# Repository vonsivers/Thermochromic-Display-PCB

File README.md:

# Thermochromic-Display-PCB
 Thermochromic Temperature & Humidity Display - PCB Version

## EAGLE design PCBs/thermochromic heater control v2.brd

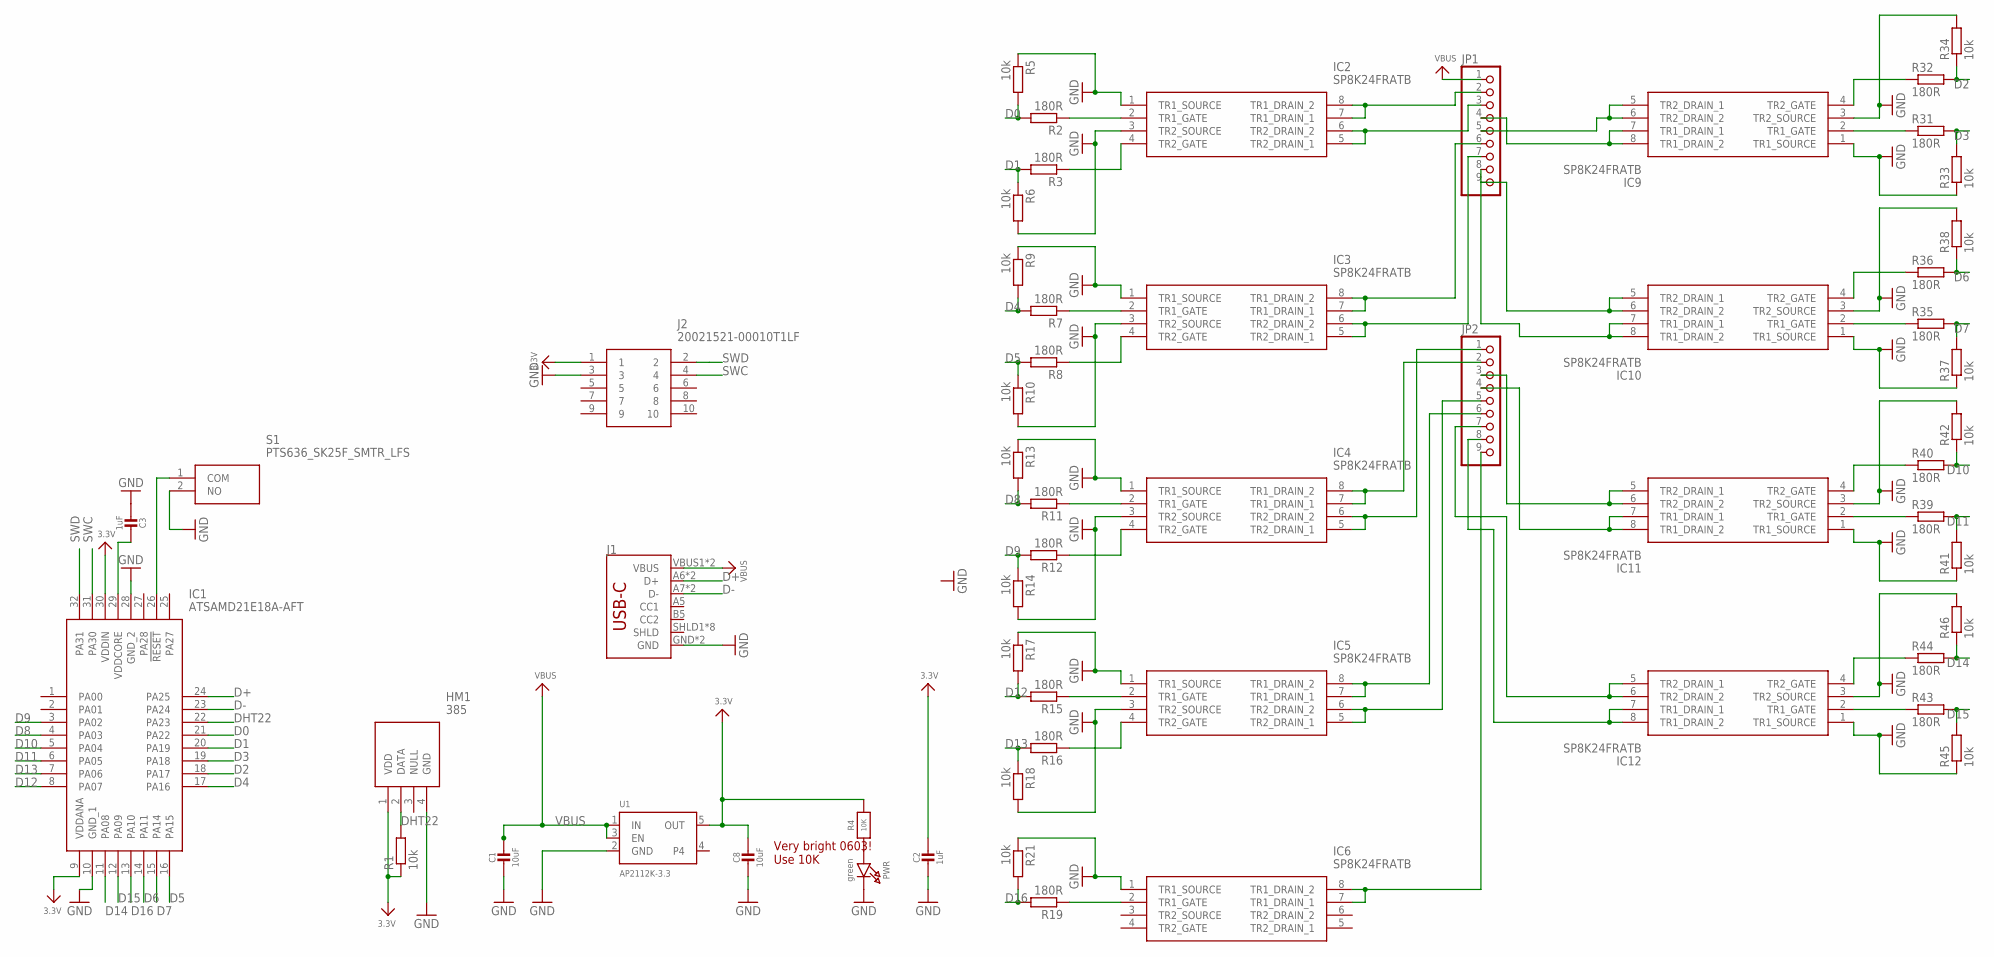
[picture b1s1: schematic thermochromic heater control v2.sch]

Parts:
C1, C8: 10uF; 0805-NO
C2, C3: 1uF; 0603-NO
HM1: 385; TO200P770X1510X2520-4P
IC1: ATSAMD21E18A-AFT; QFP80P900X900X120-32N
IC2, IC3, IC4, IC5, IC6, IC9, IC10, IC11, IC12: SP8K24FRATB; SOIC127P600X175-8N
J1: USB_C2-LAYER; USB-C-16P
J2: 20021521-00010T1LF; 2002152100010T1LF
JP1, JP2: PINHD-1X9; 1X09
PWR: green; CHIPLED_0603_NOOUTLINE
R1, R5, R6, R9, R10, R13, R14, R17, R18, R21, R33, R34, R37, R38, R41, R42, R45, R46: 10k; R0603
R2, R3, R7, R8, R11, R12, R15, R16, R19, R31, R32, R35, R36, R39, R40, R43, R44: 180R; R0603
R4: 10K; 0603-NO
S1: PTS636_SK25F_SMTR_LFS; PTS636SK25FSMTRLFS
U1: AP2112K-3.3; SOT23-5

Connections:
3.3V: C2.1, C8.1, HM1.1 (VDD), IC1.9 (VDDANA), IC1.30 (VDDIN), J2.1, R1.1, R4.2, U1.5 (OUT)
D0: IC1.21 (PA22), R2.2, R5.2
D1: IC1.20 (PA19), R3.2, R6.1
D2: IC1.18 (PA17), R32.2, R34.1
D3: IC1.19 (PA18), R31.2, R33.2
D4: IC1.17 (PA16), R7.2, R9.2
D5: IC1.16 (PA15), R8.2, R10.1
D6: IC1.14 (PA11), R36.2, R38.1
D7: IC1.15 (PA14), R35.2, R37.2
D8: IC1.4 (PA03), R11.2, R13.2
D9: IC1.3 (PA02), R12.2, R14.1
D10: IC1.5 (PA04), R40.2, R42.1
D11: IC1.6 (PA05), R39.2, R41.2
D12: IC1.8 (PA07), R15.2, R17.2
D13: IC1.7 (PA06), R16.2, R18.1
D14: IC1.11 (PA08), R44.2, R46.1
D15: IC1.12 (PA09), R43.2, R45.2
D16: IC1.13 (PA10), R19.2, R21.2
D+: IC1.24 (PA25), J1.A6 (D+), J1.B6 (D+)
D-: IC1.23 (PA24), J1.A7 (D-), J1.B7 (D-)
DHT22: HM1.2 (DATA), IC1.22 (PA23), R1.2
GND: C1.2, C2.2, C3.2, C8.2, HM1.4 (GND), IC1.10 (GND_1), IC1.28 (GND_2), IC2.1 (TR1_SOURCE), IC2.3 (TR2_SOURCE), IC3.1 (TR1_SOURCE), IC3.3 (TR2_SOURCE), IC4.1 (TR1_SOURCE), IC4.3 (TR2_SOURCE), IC5.1 (TR1_SOURCE), IC5.3 (TR2_SOURCE), IC6.1 (TR1_SOURCE), IC9.1 (TR1_SOURCE), IC9.3 (TR2_SOURCE), IC10.1 (TR1_SOURCE), IC10.3 (TR2_SOURCE), IC11.1 (TR1_SOURCE), IC11.3 (TR2_SOURCE), IC12.1 (TR1_SOURCE), IC12.3 (TR2_SOURCE), J1.GND, J1.GND2 (GND), J2.3, PWR.C, R5.1, R6.2, R9.1, R10.2, R13.1, R14.2, R17.1, R18.2, R21.1, R33.1, R34.2, R37.1, R38.2, R41.1, R42.2, R45.1, R46.2, S1.2 (NO), U1.2 (GND)
unnamed: C3.1, IC1.29 (VDDCORE)
unnamed: IC2.2 (TR1_GATE), R2.1
unnamed: IC1.26 (!RESET), S1.1 (COM)
unnamed: PWR.A, R4.1
unnamed: IC2.4 (TR2_GATE), R3.1
unnamed: IC2.7 (TR1_DRAIN_1), IC2.8 (TR1_DRAIN_2), JP1.2
unnamed: IC2.5 (TR2_DRAIN_1), IC2.6 (TR2_DRAIN_2), JP1.3
unnamed: IC10.2 (TR1_GATE), R35.1
unnamed: IC3.2 (TR1_GATE), R7.1
unnamed: IC3.4 (TR2_GATE), R8.1
unnamed: IC3.7 (TR1_DRAIN_1), IC3.8 (TR1_DRAIN_2), JP1.6
unnamed: IC3.5 (TR2_DRAIN_1), IC3.6 (TR2_DRAIN_2), JP1.7
unnamed: IC4.2 (TR1_GATE), R11.1
unnamed: IC4.4 (TR2_GATE), R12.1
unnamed: IC4.7 (TR1_DRAIN_1), IC4.8 (TR1_DRAIN_2), JP2.2
unnamed: IC4.5 (TR2_DRAIN_1), IC4.6 (TR2_DRAIN_2), JP2.1
unnamed: IC5.2 (TR1_GATE), R15.1
unnamed: IC5.4 (TR2_GATE), R16.1
unnamed: IC5.7 (TR1_DRAIN_1), IC5.8 (TR1_DRAIN_2), JP2.6
unnamed: IC5.5 (TR2_DRAIN_1), IC5.6 (TR2_DRAIN_2), JP2.5
unnamed: IC6.2 (TR1_GATE), R19.1
unnamed: IC6.7 (TR1_DRAIN_1), IC6.8 (TR1_DRAIN_2), JP2.9
unnamed: IC9.2 (TR1_GATE), R31.1
unnamed: IC9.4 (TR2_GATE), R32.1
unnamed: IC9.7 (TR1_DRAIN_1), IC9.8 (TR1_DRAIN_2), JP1.4
unnamed: IC9.5 (TR2_DRAIN_1), IC9.6 (TR2_DRAIN_2), JP1.5
unnamed: IC10.4 (TR2_GATE), R36.1
unnamed: IC10.7 (TR1_DRAIN_1), IC10.8 (TR1_DRAIN_2), JP1.8
unnamed: IC10.5 (TR2_DRAIN_1), IC10.6 (TR2_DRAIN_2), JP1.9
unnamed: IC11.2 (TR1_GATE), R39.1
unnamed: IC11.4 (TR2_GATE), R40.1
unnamed: IC11.7 (TR1_DRAIN_1), IC11.8 (TR1_DRAIN_2), JP2.4
unnamed: IC11.5 (TR2_DRAIN_1), IC11.6 (TR2_DRAIN_2), JP2.3
unnamed: IC12.2 (TR1_GATE), R43.1
unnamed: IC12.4 (TR2_GATE), R44.1
unnamed: IC12.7 (TR1_DRAIN_1), IC12.8 (TR1_DRAIN_2), JP2.8
unnamed: IC12.5 (TR2_DRAIN_1), IC12.6 (TR2_DRAIN_2), JP2.7
SWC: IC1.31 (PA30), J2.4
SWD: IC1.32 (PA31), J2.2
VBUS: C1.1, J1.VBUS1 (VBUS), J1.VBUS2 (VBUS), JP1.1, U1.1 (IN), U1.3 (EN)

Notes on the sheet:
Very bright 0603! Use 10K

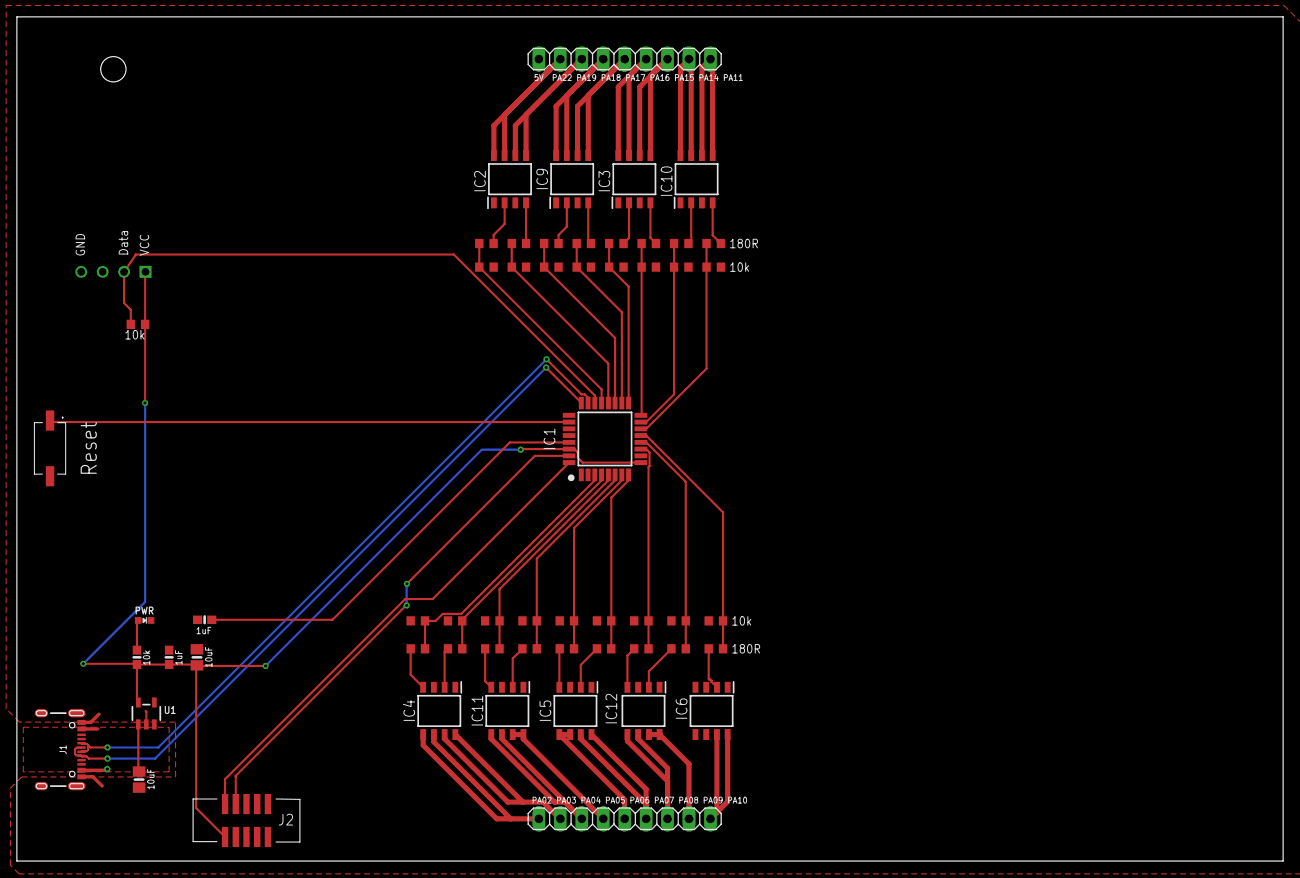
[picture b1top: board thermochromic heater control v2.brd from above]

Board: 2 copper layers, 149.9 x 99.9 mm, 58 parts (1 on the bottom side), 62 nets.

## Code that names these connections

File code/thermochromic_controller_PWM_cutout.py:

from microcontroller import delay_us
from microcontroller import pin
import digitalio
import time
import adafruit_dht
# import random

temp_unit = "C"         # temperature unit ("C" or "F")
dutycycle = 0.055        # PWM duty cycle (0 to 0.058)
frequency = 100.       # PWM frequency (Hz)

# heating time is linearly interpolated between two points
P1 = [26, 3.5, 55]  # first point [temperature (°C/F), heating time (s), cooling time (s)]
P2 = [21, 6.5, 30]   # second point [temperature (°C/F), heating time (s), cooling time (s)]

# t_cool = 30             # cooling duration (s)

# reduction factor of duty cycle if segment was heated before
f_reduce = 0.55

seg1E = digitalio.DigitalInOut(pin.PA02)
seg1G = digitalio.DigitalInOut(pin.PA03)
seg1D = digitalio.DigitalInOut(pin.PA04)
seg1C = digitalio.DigitalInOut(pin.PA05)
seg2E = digitalio.DigitalInOut(pin.PA06)
seg2G = digitalio.DigitalInOut(pin.PA07)
seg2D = digitalio.DigitalInOut(pin.PA08)
seg2C = digitalio.DigitalInOut(pin.PA09)
segD2 = digitalio.DigitalInOut(pin.PA10)
segD3 = digitalio.DigitalInOut(pin.PA11)
segD1 = digitalio.DigitalInOut(pin.PA14)
seg2B = digitalio.DigitalInOut(pin.PA15)
seg2A = digitalio.DigitalInOut(pin.PA16)
seg2F = digitalio.DigitalInOut(pin.PA17)
seg1B = digitalio.DigitalInOut(pin.PA18)
seg1A = digitalio.DigitalInOut(pin.PA19)
seg1F = digitalio.DigitalInOut(pin.PA22)

seg1A.direction = digitalio.Direction.OUTPUT
seg1B.direction = digitalio.Direction.OUTPUT
seg1C.direction = digitalio.Direction.OUTPUT
seg1D.direction = digitalio.Direction.OUTPUT
seg1E.direction = digitalio.Direction.OUTPUT
seg1F.direction = digitalio.Direction.OUTPUT
seg1G.direction = digitalio.Direction.OUTPUT
seg2A.direction = digitalio.Direction.OUTPUT
seg2B.direction = digitalio.Direction.OUTPUT
seg2C.direction = digitalio.Direction.OUTPUT
seg2D.direction = digitalio.Direction.OUTPUT
seg2E.direction = digitalio.Direction.OUTPUT
seg2F.direction = digitalio.Direction.OUTPUT
seg2G.direction = digitalio.Direction.OUTPUT
segD1.direction = digitalio.Direction.OUTPUT
segD2.direction = digitalio.Direction.OUTPUT
segD3.direction = digitalio.Direction.OUTPUT

# Initial the dht device, with data pin connected to:
dhtDevice = adafruit_dht.DHT22(pin.PA23)

# last heated segments
seg_last = []

# adjust factor for heating duration of each segment
def adjust_factor(pinname):
    if pinname == seg1A:
        return 1.
    elif pinname == seg1B:
        return 1.
    elif pinname == seg1C:
        return 1.
    elif pinname == seg1D:
        return 1.25
    elif pinname == seg1E:
        return 1.
    elif pinname == seg1F:
        return 1.
    elif pinname == seg1G:
        return 1.
    elif pinname == seg2A:
        return 1.
    elif pinname == seg2B:
        return 1.
    elif pinname == seg2C:
        return 1.
    elif pinname == seg2D:
        return 1.2
    elif pinname == seg2E:
        return 1.
    elif pinname == seg2F:
        return 1
    elif pinname == seg2G:
        return 1
    elif pinname == segD1:
        return 1.
    elif pinname == segD2:
        return 1.
    elif pinname == segD3:
        return 8.5
    else:
        return 0


# calculate heating time through linear interpolation
def CalcHeat(T):
    global P1, P2
    # print("heating time:")
    # print((T - P1[0]) * (P2[1] - P1[1]) / (P2[0] - P1[0]) + P1[1])
    return (T - P1[0]) * (P2[1] - P1[1]) / (P2[0] - P1[0]) + P1[1]

# calculate cooling time through linear interpolation
def CalcCool(T):
    global P1, P2
    # print("heating time:")
    # print((T - P1[0]) * (P2[1] - P1[1]) / (P2[0] - P1[0]) + P1[1])
    return (T - P1[0]) * (P2[2] - P1[2]) / (P2[0] - P1[0]) + P1[2]

# convert number to segments
# unit = empty or "%"
def num2seg(number, unit=""):
    segments1 = {
        1: [seg1B, seg1C],
        2: [seg1A, seg1B, seg1D, seg1E, seg1G],
        3: [seg1A, seg1B, seg1C, seg1D, seg1G],
        4: [seg1F, seg1B, seg1G, seg1C],
        5: [seg1A, seg1F, seg1G, seg1C, seg1D],
        6: [seg1A, seg1F, seg1G, seg1E, seg1C, seg1D],
        7: [seg1A, seg1B, seg1C],
        8: [seg1A, seg1B, seg1C, seg1D, seg1E, seg1F, seg1G],
        9: [seg1A, seg1B, seg1C, seg1D, seg1F, seg1G]

    }
    segments2 = {
        0: [seg2A, seg2B, seg2C, seg2D, seg2E, seg2F],
        1: [seg2B, seg2C],
        2: [seg2A, seg2B, seg2D, seg2E, seg2G],
        3: [seg2A, seg2B, seg2C, seg2D, seg2G],
        4: [seg2F, seg2B, seg2G, seg2C],
        5: [seg2A, seg2F, seg2G, seg2C, seg2D],
        6: [seg2A, seg2F, seg2G, seg2E, seg2C, seg2D],
        7: [seg2A, seg2B, seg2C],
        8: [seg2A, seg2B, seg2C, seg2D, seg2E, seg2F, seg2G],
        9: [seg2A, seg2B, seg2C, seg2D, seg2F, seg2G]
    }

    number = round(number)
    number1 = int(number/10)
    number2 = number % 10
    print("digit 1:")
    print(number1)
    print("digit 2:")
    print(number2)
    if number1 > 0:
        digit1 = segments1.get(number1)
    else:
        digit1 = []
    digit2 = segments2.get(number2)
    segments = digit1 + digit2 + [segD1]
    # segments.append(segD1)
    if unit == "%":
        segments += [segD2, segD3]
    return segments

# read DHT22
def readDHT():
    try:
        # Print the values to the serial port
        temperature_c = dhtDevice.temperature
        # temperature_c = random.uniform(15, 35)
        temperature_f = temperature_c * (9 / 5) + 32
        humidity = dhtDevice.humidity
        # humidity = random.uniform(20, 90)
        print("Temp: {:.1f} F / {:.1f} C    Humidity: {}% "
              .format(temperature_f, temperature_c, humidity))
        if temp_unit == "C":
            return temperature_c, humidity
        elif temp_unit == "F":
            return temperature_f, humidity

    except RuntimeError as error:
        # Errors happen fairly often, DHT's are hard to read, just keep going
        print(error.args[0])
        return 0


# check if pinname is in list
def compare(pinname1, pinnames):
    for pinname2 in pinnames:
        if pinname1 == pinname2:
            return 1
    return 0

# create fake PWM signal
def fakePWM(pinnames, pinnames_last, duration):
    global dutycycle
    global frequency
    global adjust_factor
    global f_reduce
    T = 1./frequency                    # period in s
    ontime = T*dutycycle*1e6            # on time in µs
    offtime = T*(1-dutycycle)*1e6       # off time in µs
    cycles = int(duration/T)            # number of cycles
    npins = len(pinnames)               # number of segments
    # print("ontime: {:.0f} us" .format(ontime))
    # print("offtime: {:.0f} us" .format(offtime))
    # print("cycles: {:.0f}" .format(cycles))
    # print("npins: {:.0f}" .format(npins))

    # calculate on time for each segment
    ontime_adjusted = []
    for pinname in pinnames:
        if compare(pinname, pinnames_last):
            # reduce duration if element was heated before
            ontime_adjusted.append(f_reduce*ontime*adjust_factor(pinname))
        else:
            ontime_adjusted.append(ontime*adjust_factor(pinname))
    dt = offtime-sum(ontime_adjusted)+ontime_adjusted[0]       # delay at end of pulse cycle
    # print("dt: {:.0f} us" .format(dt))
    # print("total duration: {:.0f} us" .format(sum(ontime_adjusted)+dt))
    if dt < 0.:
        dt = 0.
    # heat segments
    for i in range(cycles):
        # to limit current segments are heated one after another
        j = 0
        for pinname in pinnames:
            pinname.value = True
            delay_us(int(ontime_adjusted[j]))
            pinname.value = False
            j += 1
        delay_us(int(dt))

    return

time.sleep(2)

while True:
    DHT_data = readDHT()
    if DHT_data:
        print("showing temperature")
        seg = num2seg(DHT_data[0])              # temperature
        print("heating ...")
        fakePWM(seg, seg_last, CalcHeat(DHT_data[0]))
        seg_last = seg
        print("cooling ...")
        time.sleep(CalcCool(DHT_data[0]))
    DHT_data = readDHT()
    if DHT_data:
        print("showing humidity")
        seg = num2seg(DHT_data[1], unit="%")          # humidity
        print("heating ...")
        fakePWM(seg, seg_last, CalcHeat(DHT_data[0]))
        seg_last = seg
        print("cooling ...")
        time.sleep(CalcCool(DHT_data[0]))

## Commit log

2020-03-16 updated bootloader

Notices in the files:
parts and their libraries:
microbuilder: This work is placed in the public domain, and may be freely used for commercial and non-commercial work with the following conditions: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
SparkFun-Connectors: Licensing: Creative Commons ShareAlike 4.0 International - https://creativecommons.org/licenses/by-sa/4.0
